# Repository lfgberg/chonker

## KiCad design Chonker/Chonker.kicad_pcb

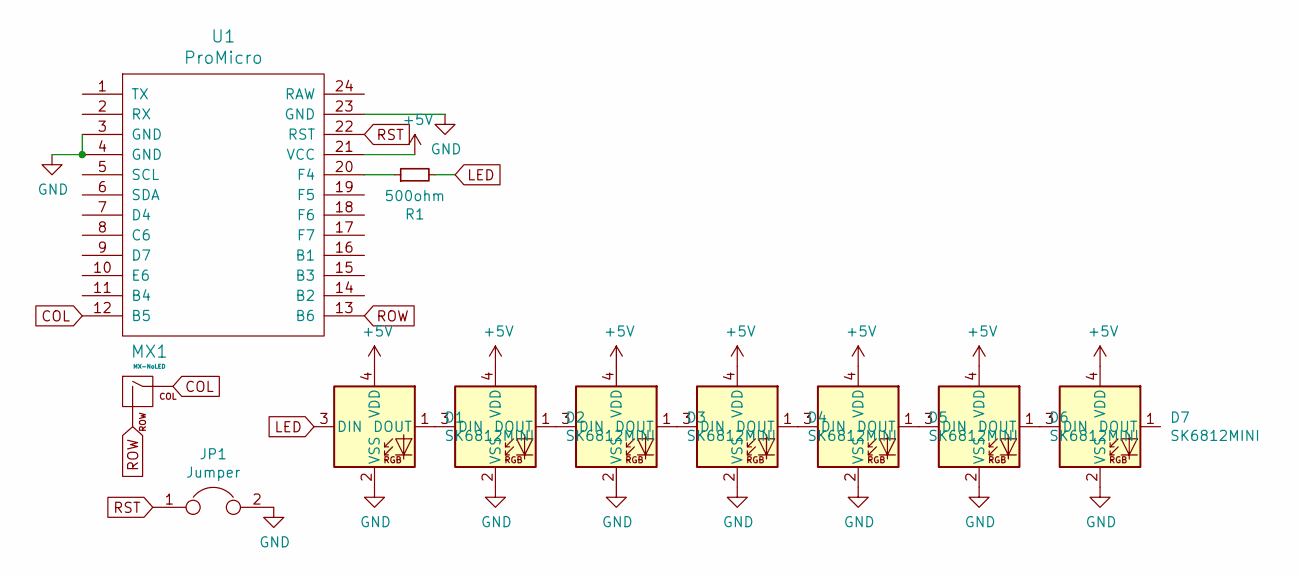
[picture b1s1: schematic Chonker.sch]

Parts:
D1, D2, D3, D4, D5, D6, D7: SK6812MINI; LED_SK6812MINI_PLCC4_3.5x3.5mm_P1.75mm
JP1: Jumper; ResetJumper
MX1: MX-NoLED; kailh_big_series
R1: 500ohm; R_0805_2012Metric
U1: ProMicro; promicro-alligning-silk-front-only

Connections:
+5V: D1.4 (VDD), D2.4 (VDD), D3.4 (VDD), D4.4 (VDD), D5.4 (VDD), D6.4 (VDD), D7.4 (VDD), U1.21 (VCC)
COL: MX1.1 (COL), U1.12 (B5)
GND: D1.2 (VSS), D2.2 (VSS), D3.2 (VSS), D4.2 (VSS), D5.2 (VSS), D6.2 (VSS), D7.2 (VSS), JP1.2, U1.3 (GND), U1.4 (GND), U1.23 (GND)
LED: D1.3 (DIN), R1.2
unnamed: D1.1 (DOUT), D2.3 (DIN)
unnamed: D2.1 (DOUT), D3.3 (DIN)
unnamed: D3.1 (DOUT), D4.3 (DIN)
unnamed: D4.1 (DOUT), D5.3 (DIN)
unnamed: D5.1 (DOUT), D6.3 (DIN)
unnamed: D6.1 (DOUT), D7.3 (DIN)
unnamed: R1.1, U1.20 (F4)
ROW: MX1.2 (ROW), U1.13 (B6)
RST: JP1.1, U1.22 (RST)

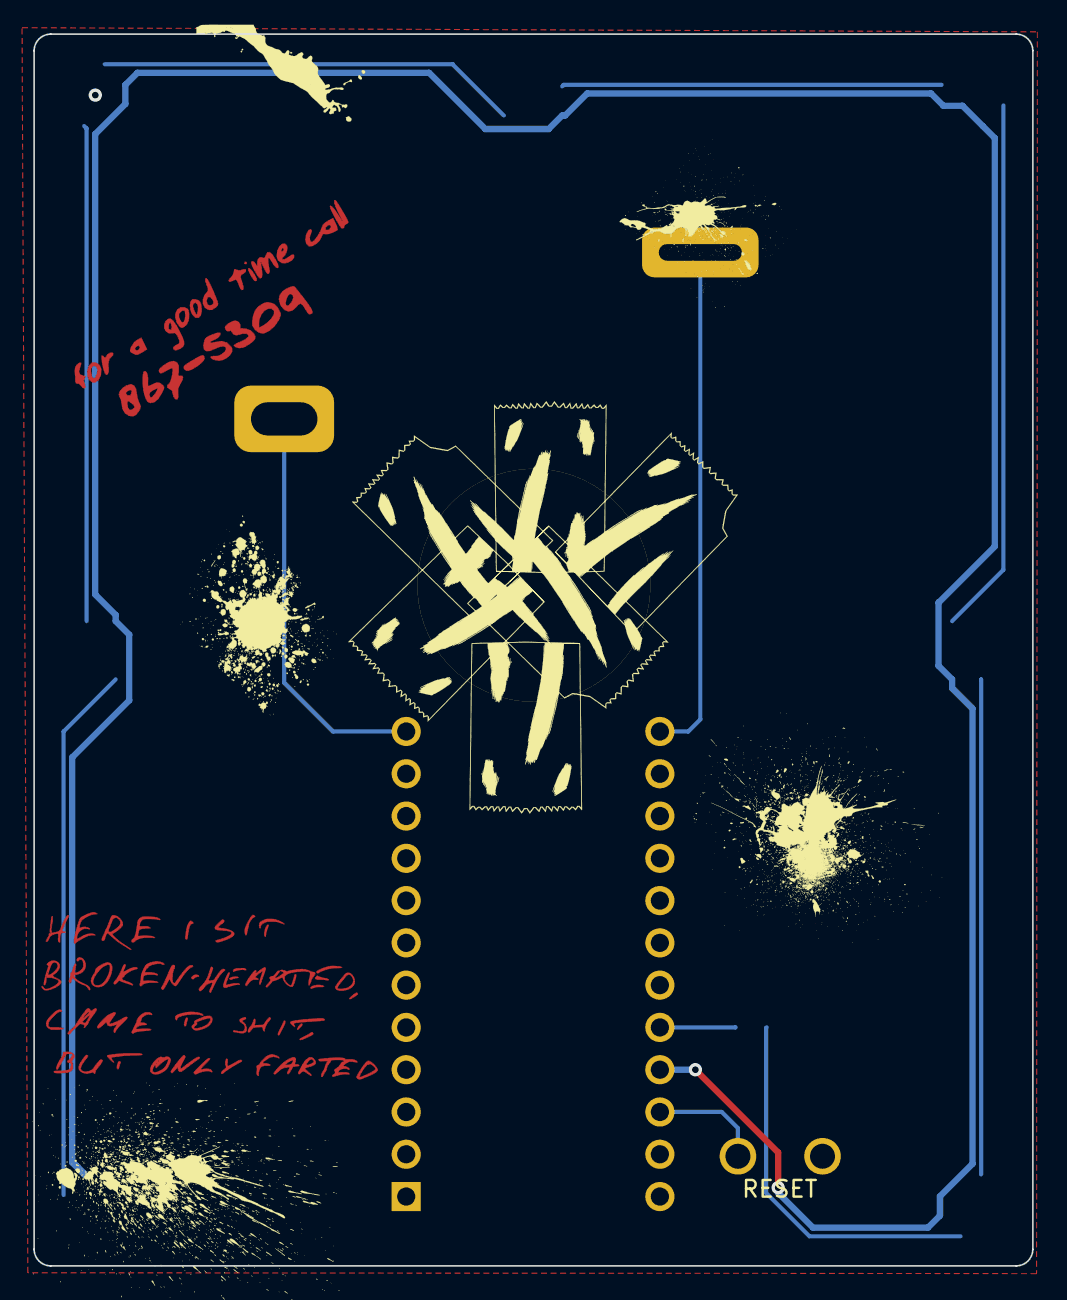
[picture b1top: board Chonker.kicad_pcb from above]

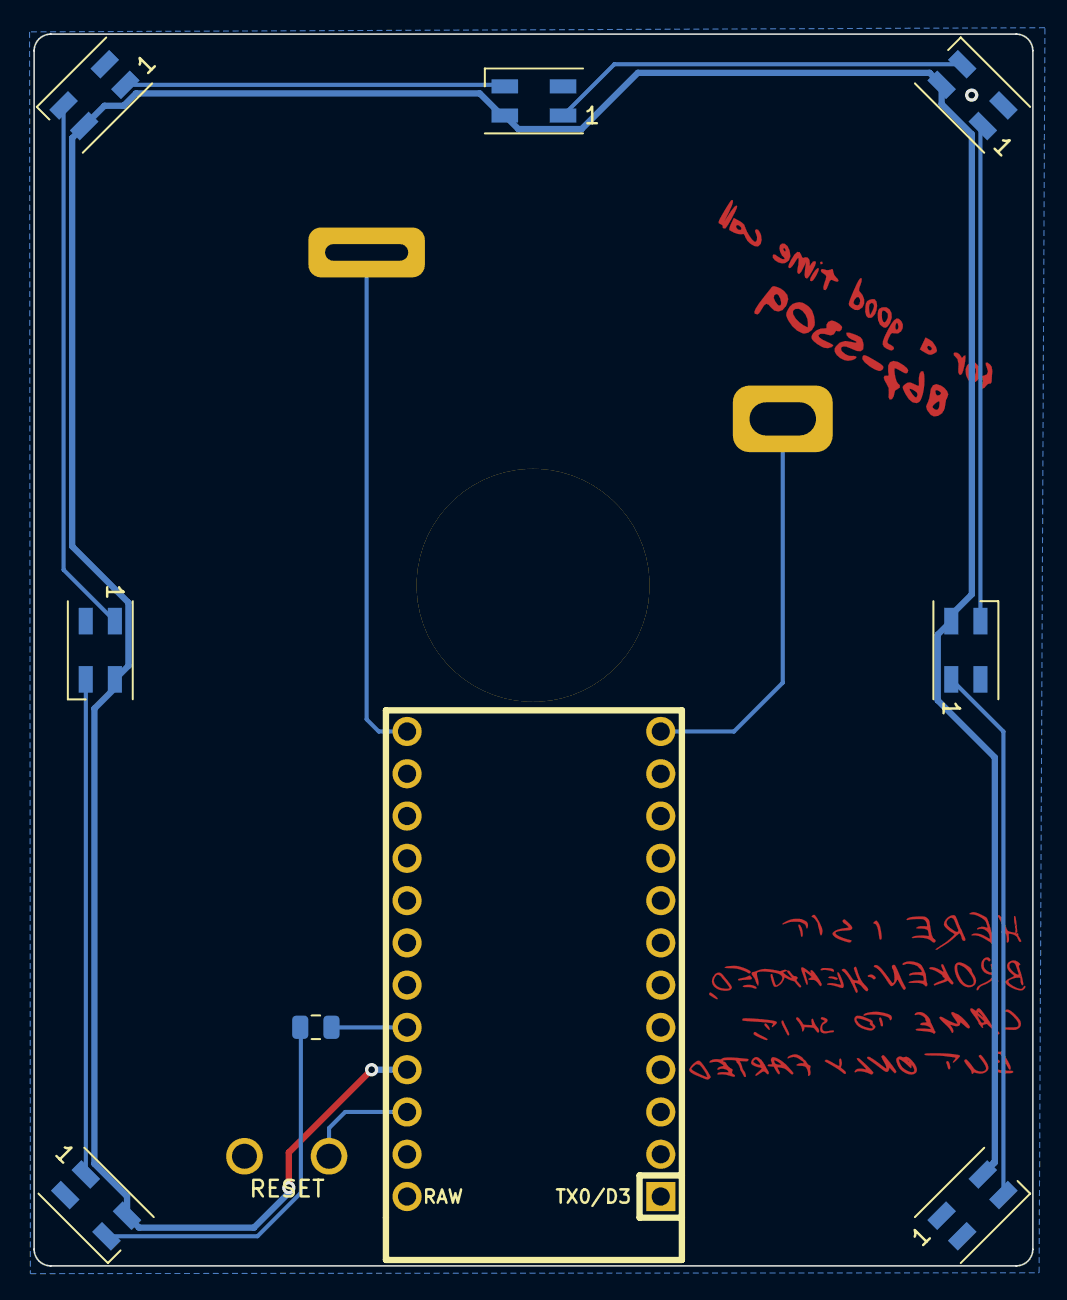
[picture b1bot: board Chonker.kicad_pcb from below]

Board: 2 copper layers, 60.0 x 74.0 mm, 12 parts (9 on the bottom side), 13 nets.

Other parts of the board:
de: LOGO; tape-2

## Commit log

2021-04-05 .
    .
2021-04-05 Update LICENSE
